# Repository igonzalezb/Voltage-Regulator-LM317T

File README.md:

# Voltage Regulator LM317T

* [Interactive BOM](https://htmlpreview.github.io/?https://github.com/igonzalezb/Voltage-Regulator-LM317T/blob/main/bom/ibom.html)

## Schematic

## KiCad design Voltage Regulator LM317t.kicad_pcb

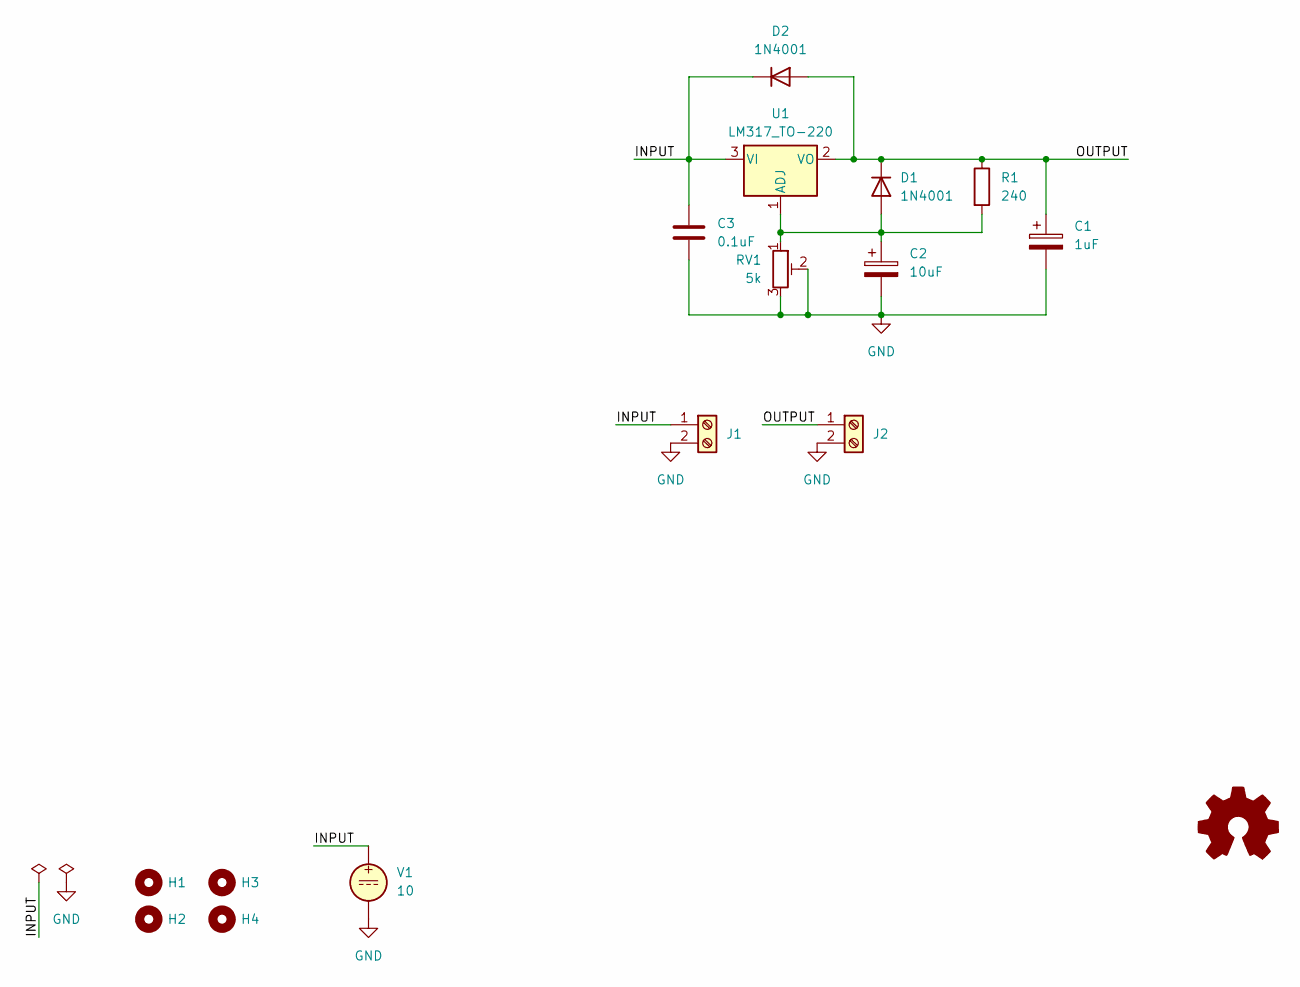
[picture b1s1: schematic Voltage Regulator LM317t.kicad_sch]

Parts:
C1: 1uF; CP_Radial_D5.0mm_P2.50mm
C2: 10uF; CP_Radial_D5.0mm_P2.50mm
C3: 0.1uF; C_Disc_D8.0mm_W5.0mm_P5.00mm
D1, D2: 1N4001; D_DO-41_SOD81_P10.16mm_Horizontal
H1, H2, H3, H4: MountingHole; MountingHole_2.1mm
J1: IN; TerminalBlock_bornier-2_P5.08mm
J2: OUT; TerminalBlock_bornier-2_P5.08mm
R1: 240; R_Axial_DIN0207_L6.3mm_D2.5mm_P10.16mm_Horizontal
RV1: 5k; Potentiometer_Bourns_3296W_Vertical
SYM1: Logo_Open_Hardware_Small; OSHW-Symbol_6.7x6mm_Copper
U1: LM317_TO-220; TO-220-3_Vertical
V1: 10

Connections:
/INPUT: C3.1, D2.1 (K), J1.1, U1.3 (VI), V1.1
/OUTPUT: C1.1, D1.1 (K), D2.2 (A), J2.1, R1.1, U1.2 (VO)
GND: C1.2, C2.2, C3.2, J1.2, J2.2, RV1.2, RV1.3, V1.2
unnamed: C2.1, D1.2 (A), R1.2, RV1.1, U1.1 (ADJ)

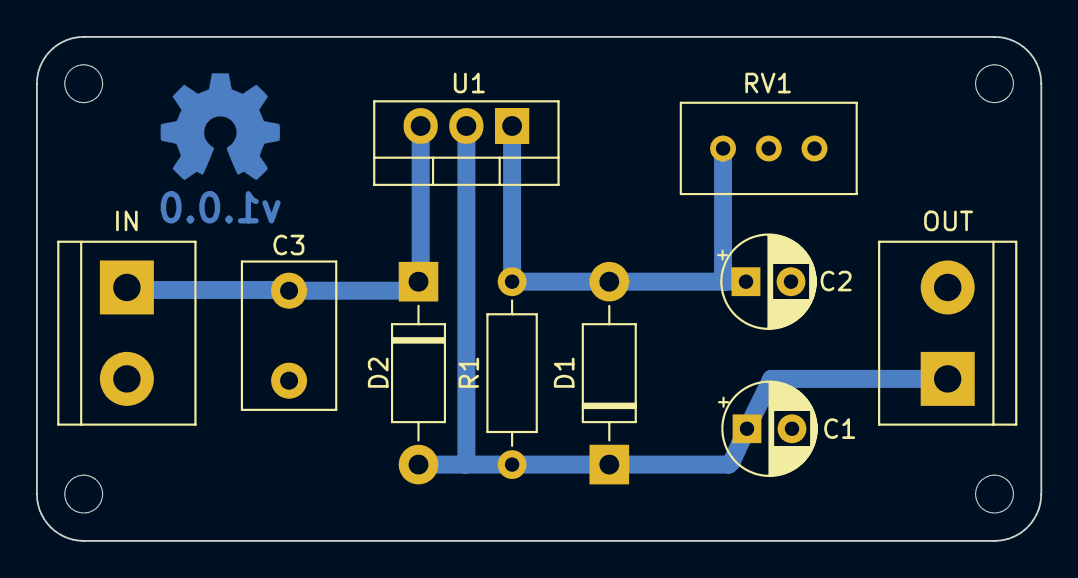
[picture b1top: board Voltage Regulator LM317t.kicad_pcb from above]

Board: 2 copper layers, 55.8 x 28.0 mm, 15 parts (1 on the bottom side), 4 nets.

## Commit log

2023-08-13 update gitignore
2023-08-13 renders
2023-08-13 simulation
2023-08-16 interactive bom
